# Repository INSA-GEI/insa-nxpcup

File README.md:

# insa-nxpcup

Repository for INSA NXP cup 

# File organization
- **buggy_kl25z**: contain code, documentation, and hardware design of the Buggy with FRMD_KL25Z board (2 oldest buggies) 
- **guides**: useful guides for everyone 
- **archive**: all the work before 2023

# How can I navigate this project?
Each buggy has a dedicated directory with all the code and hardware files.

The source code for a specific buggy can be found at `buggy_name/code/buggy`

It contains the source code for each component and also the main source code of the buggy. 

**There is a README.md in the `code` folder that describes how to work with the code. Please refer to that document.**

# Prerequisite
### *MCU Xpresso*

IDE to work with NXP board, not intuitive to use but has auto-configuration tool.

- **Install [link](https://nxp.flexnetoperations.com/control/frse/product?entitlementId=107109928&lineNum=1&authContactId=81844998&authPartyId=54297698)**
- A guide is available [here](./guides/guide_mcuxpresso.md)

**`WARNING for Windows users!!!`** When installing and using MCU Xpresso, a **firewall window** will pop up that asks you to permit the app to access public and private networks. The same will happen the first time you flash/ debug the code.

**Make sure to permit `both` private and public networks**.

Failed to do so then good luck getting the Redlink server working without reinstalling Windows.

### *Git and GitHub*
- Check [here](./guides/guide_git.md) for a quick guide on how to install and use Git.

# Quick HowTo
Small survival kit for everyone : 
## Installing git (the clean way)
[Get here](https://git-scm.com/downloads) and follow the installer's instructions. One should avoid using the GitHub desktop client.

## Downloading the code
```bash
git clone https://github.com/INSA-GEI/insa-nxpcup.git
cd insa-nxpcup
```

## Update before you start working!
```bash
git pull 
```
If it doesn't work, save your changes elsewhere, and retry with
```bash
git stash	#Cancels all your changes in the repo
git pull	#Try pulling again
```

## Uploading your work
Upload as often as possible. Most errors here appear when working un un-updated code.

```bash
git add .
git commit -m "Message to describe commit"
git push #Sends the previous commit on this repo
```

**NB:** A good commit message is brief, and completes the following statement: *This commit will ...*.

# Branches management
**Do not use the master branch!**

You are in branch master, nothing should be done here

Select a valid branch:
```bash
git checkout branch_name
```

Teamwork should use a main branch and integrate inside every stable work. 

**Create new branches derive from the team's main branch for your work in progress.**

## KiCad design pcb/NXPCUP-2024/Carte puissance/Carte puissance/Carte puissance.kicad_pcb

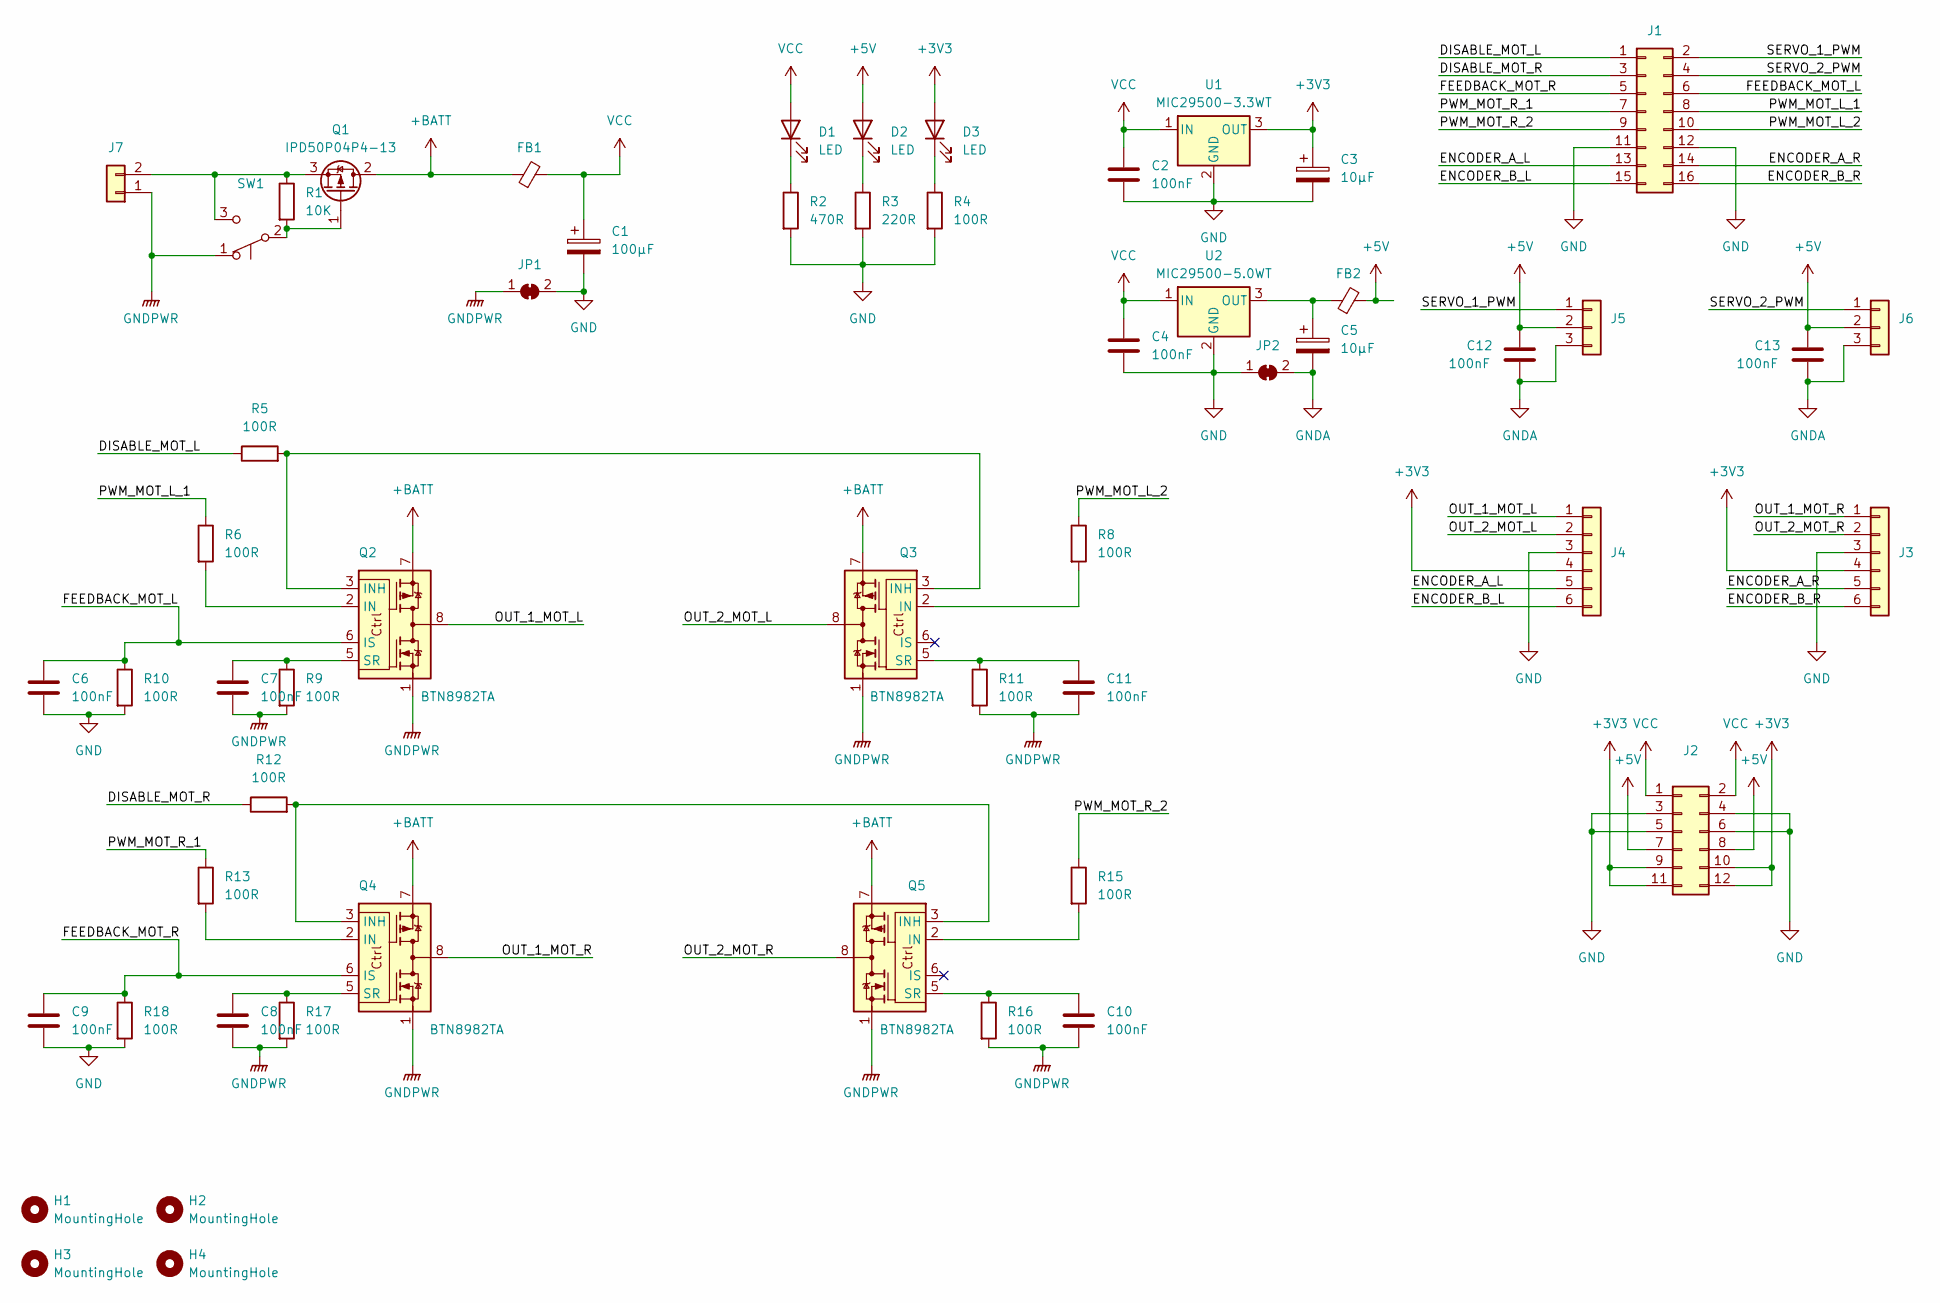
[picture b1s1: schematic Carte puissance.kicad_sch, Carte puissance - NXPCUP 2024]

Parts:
C1: 100µF; CP_Radial_D8.0mm_P3.80mm
C2, C4, C6, C7, C8, C9, C10, C11, C12, C13: 100nF; C_0805_2012Metric
C3, C5: 10µF; CP_Radial_D8.0mm_P3.80mm
D1, D2, D3: LED; LED_D3.0mm
FB1, FB2: FerriteBead_Small; L_1206_3216Metric
H1, H2, H3, H4: MountingHole; MountingHole_3.2mm_M3
J1: Conn_02x08_Odd_Even; PinHeader_2x08_P2.54mm_Vertical
J2: Conn_02x06_Odd_Even; PinHeader_2x06_P2.54mm_Vertical
J3, J4: Conn_01x06; PinHeader_1x06_P2.54mm_Vertical
J5, J6: Conn_01x03; PinHeader_1x03_P2.54mm_Vertical
J7: Conn_01x02; PinHeader_1x02_P2.54mm_Vertical
JP1, JP2: SolderJumper_2_Bridged; SolderJumper-2_P1.3mm_Bridged2Bar_Pad1.0x1.5mm
Q1: IPD50P04P4-13; SOT-23-3
Q2, Q3, Q4, Q5: BTN8982TA; TO-263-7_TabPin8
R1: 10K; R_0805_2012Metric
R2: 470R; R_0805_2012Metric
R3: 220R; R_0805_2012Metric
R4, R5, R6, R8, R9, R10, R11, R12, R13, R15, R16, R17, R18: 100R; R_0805_2012Metric
SW1: SW_Push_SPDT; SW_Slide_1P2T_CK_OS102011MS2Q
U1: MIC29500-3.3WT; TO-252-3_TabPin4
U2: MIC29500-5.0WT; TO-252-3_TabPin4

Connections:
+3V3: C3.1, D3.2 (A), J2.9, J2.10, J2.11, J2.12, J3.4, J4.4, U1.3 (OUT)
+5V: C12.2, C13.2, D2.2 (A), FB2.2, J2.7, J2.8, J5.2, J6.2
+BATT: FB1.1, Q1.2 (D), Q2.7, Q3.7, Q4.7, Q5.7
/DISABLE_MOT_L: J1.1, R5.1
/DISABLE_MOT_R: J1.3, R12.1
/ENCODER_A_L: J1.13, J4.5
/ENCODER_A_R: J1.14, J3.5
/ENCODER_B_L: J1.15, J4.6
/ENCODER_B_R: J1.16, J3.6
/FEEDBACK_MOT_L: C6.1, J1.6, Q2.6 (IS), R10.1
/FEEDBACK_MOT_R: C9.1, J1.5, Q4.6 (IS), R18.1
/OUT_1_MOT_L: J4.1, Q2.4, Q2.8
/OUT_1_MOT_R: J3.1, Q4.4, Q4.8
/OUT_2_MOT_L: J4.2, Q3.4, Q3.8
/OUT_2_MOT_R: J3.2, Q5.4, Q5.8
/PWM_MOT_L_1: J1.8, R6.1
/PWM_MOT_L_2: J1.10, R8.1
/PWM_MOT_R_1: J1.7, R13.1
/PWM_MOT_R_2: J1.9, R15.1
/SERVO_1_PWM: J1.2, J5.1
/SERVO_2_PWM: J1.4, J6.1
GND: C1.2, C2.2, C3.2, C4.2, C6.2, C9.2, J1.11, J1.12, J2.3, J2.4, J2.5, J2.6, J3.3, J4.3, JP1.2 (B), JP2.1 (A), R2.2, R3.2, R4.2, R10.2, R18.2, U1.2 (GND), U2.2 (GND)
GNDA: C5.2, C12.1, C13.1, J5.3, J6.3, JP2.2 (B)
GNDPWR: C7.2, C8.2, C10.2, C11.2, J7.1, JP1.1 (A), Q2.1, Q3.1, Q4.1, Q5.1, R9.2, R11.2, R16.2, R17.2, SW1.1 (A)
unnamed: D1.1 (K), R2.1
unnamed: D2.1 (K), R3.1
unnamed: D3.1 (K), R4.1
unnamed: J7.2, Q1.3 (S), R1.1, SW1.3 (C)
unnamed: Q1.1 (G), R1.2, SW1.2 (B)
unnamed: Q2.2 (IN), R6.2
unnamed: Q2.3 (INH), Q3.3 (INH), R5.2
unnamed: C7.1, Q2.5 (SR), R9.1
unnamed: Q3.2 (IN), R8.2
unnamed: C11.1, Q3.5 (SR), R11.1
unnamed: Q4.2 (IN), R13.2
unnamed: Q4.3 (INH), Q5.3 (INH), R12.2
unnamed: C8.1, Q4.5 (SR), R17.1
unnamed: Q5.2 (IN), R15.2
unnamed: C10.1, Q5.5 (SR), R16.1
unnamed: C5.1, FB2.1, U2.3 (OUT)
VCC: C1.1, C2.1, C4.1, D1.2 (A), FB1.2, J2.1, J2.2, U1.1 (IN), U2.1 (IN)

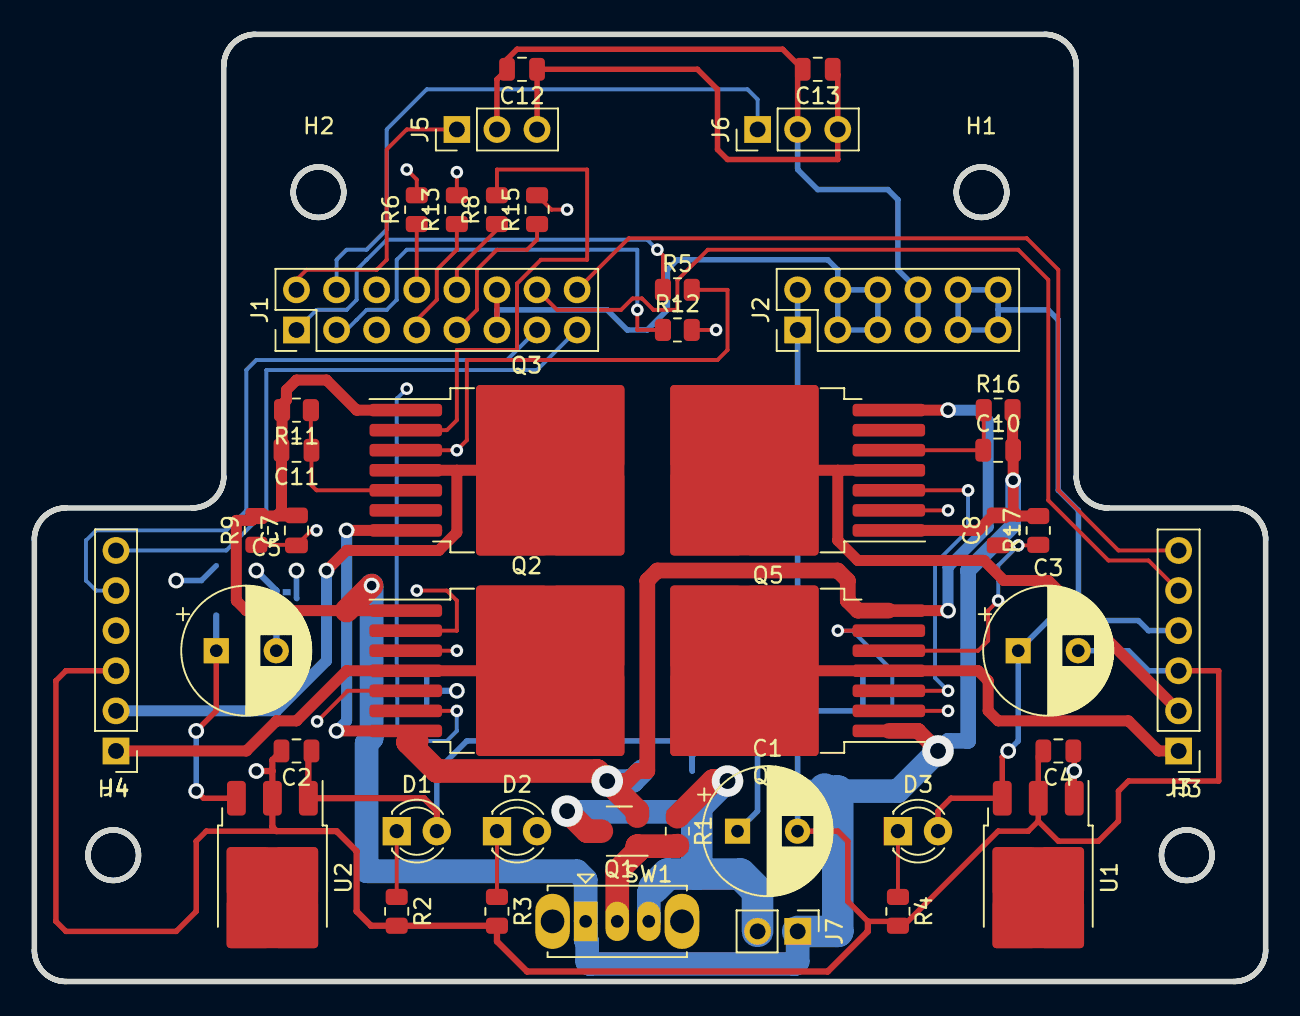
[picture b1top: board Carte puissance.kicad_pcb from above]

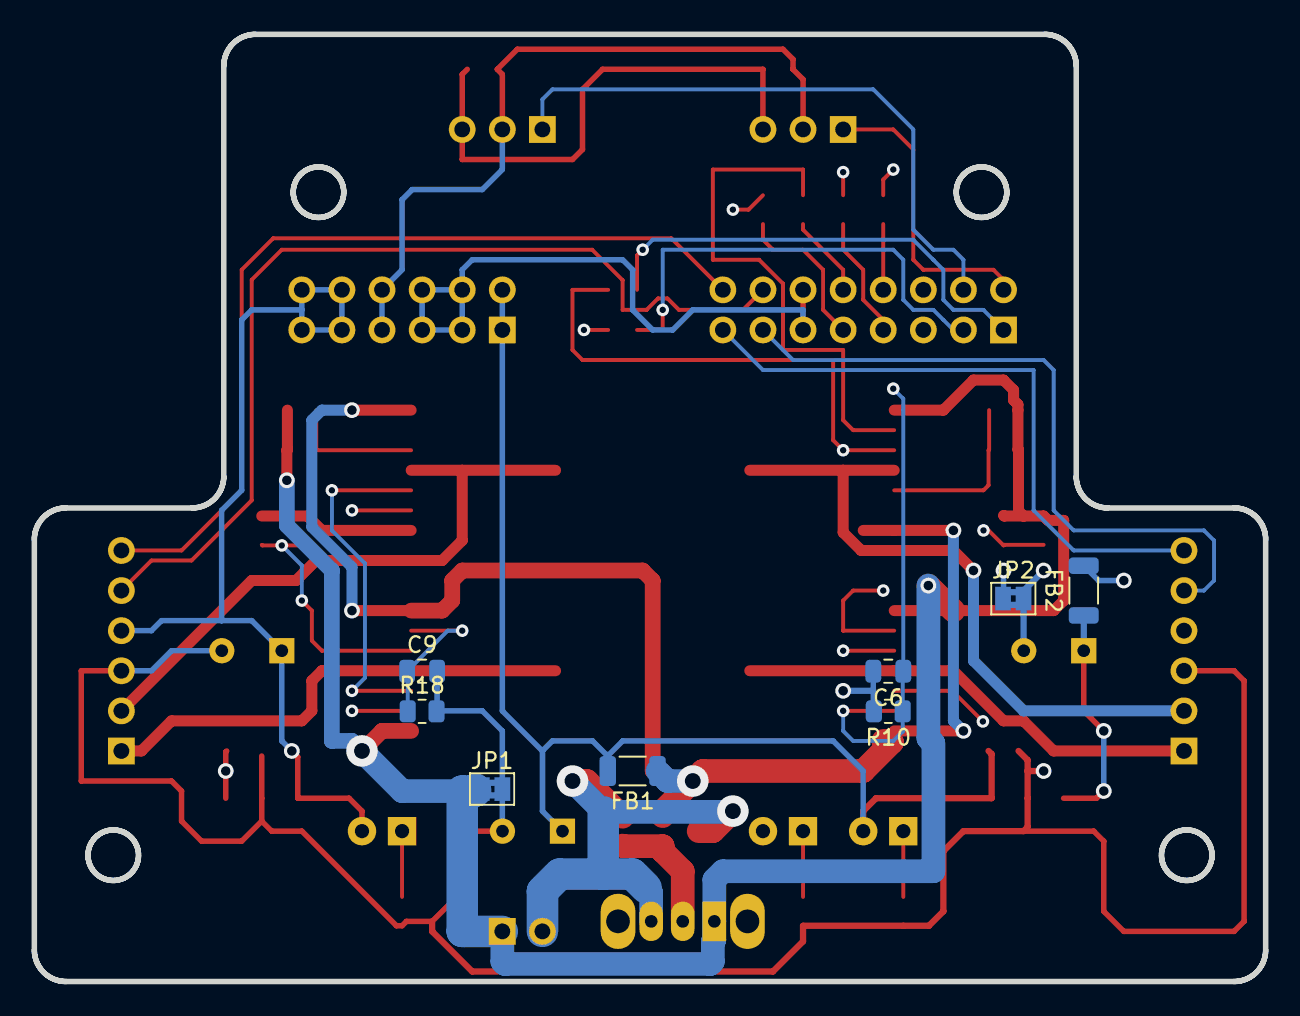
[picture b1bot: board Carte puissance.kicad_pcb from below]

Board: 4 copper layers, 78.0 x 60.0 mm, 55 parts (8 on the bottom side), 41 nets.

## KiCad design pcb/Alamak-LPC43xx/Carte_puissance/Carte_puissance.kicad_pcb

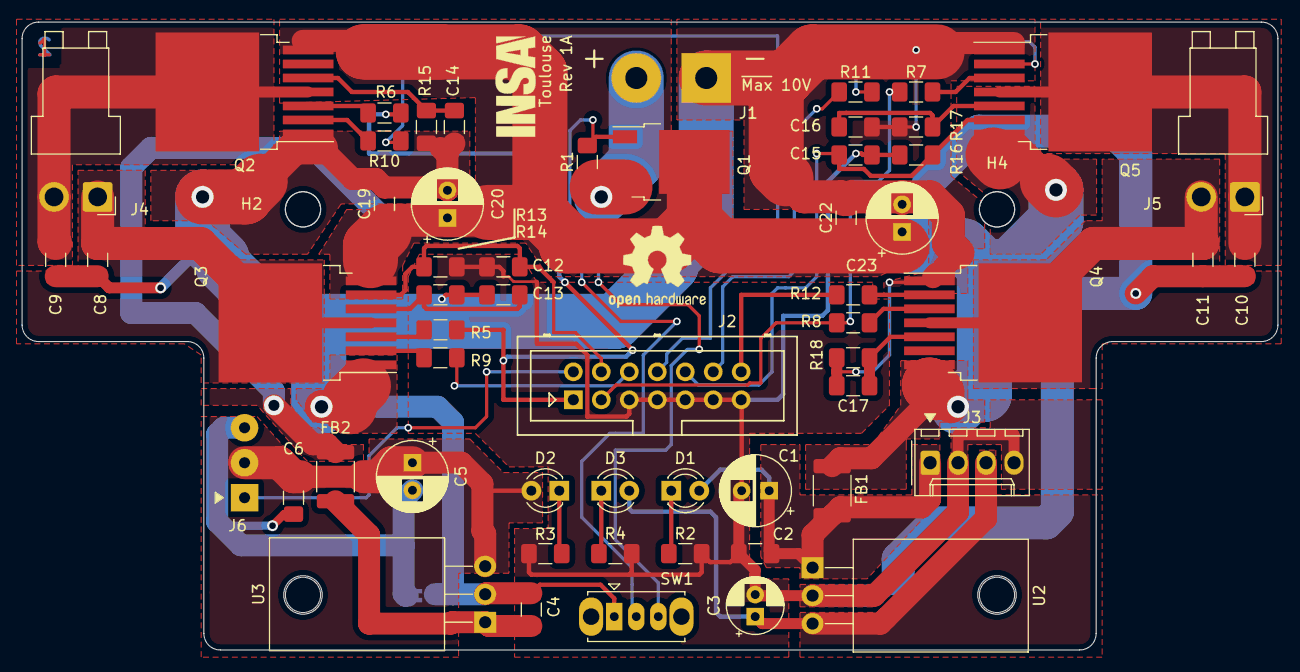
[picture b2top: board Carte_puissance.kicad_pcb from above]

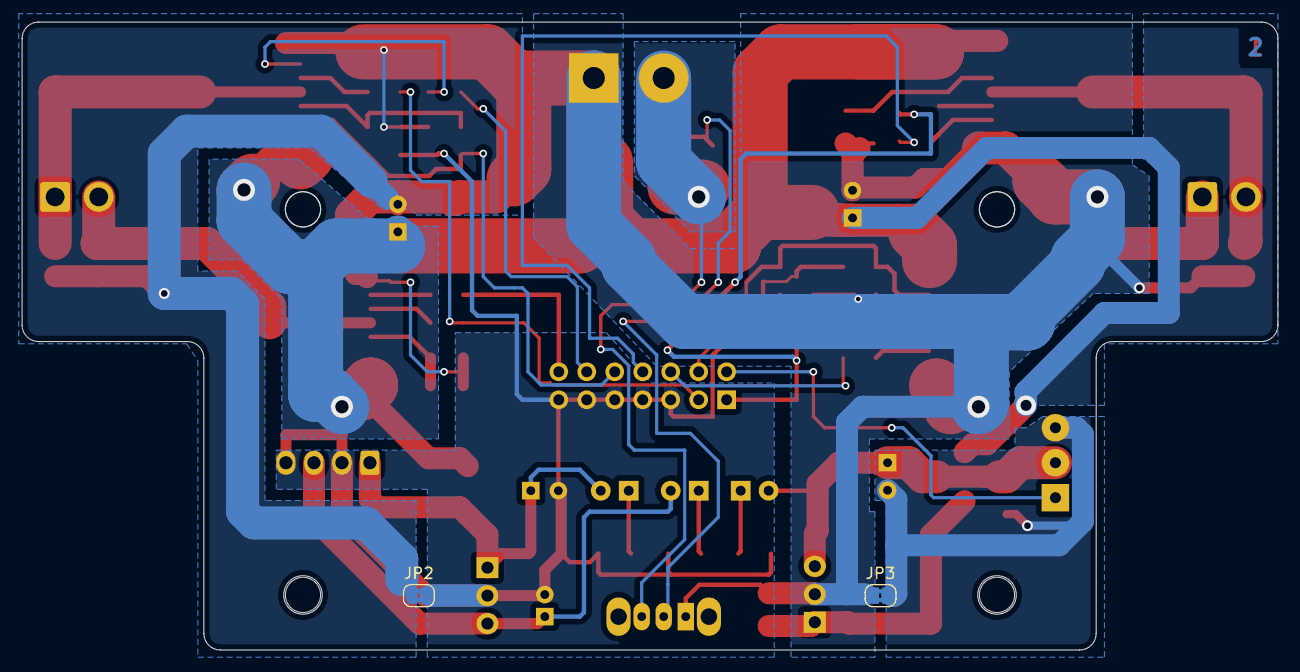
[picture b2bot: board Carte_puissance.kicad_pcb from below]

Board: 2 copper layers, 114.0 x 57.0 mm, 63 parts (2 on the bottom side), 38 nets.

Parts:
C1, C5: 100µF; CP_Radial_D6.3mm_P2.50mm
C2, C4, C6, C8, C9, C10, C11, C13, C14, C16, C17, C19, C22: 100nF; C_1206_3216Metric_Pad1.42x1.75mm_HandSolder
C3: 10µF; CP_Radial_D5.0mm_P2.00mm
C12, C15: 1nF; C_1206_3216Metric_Pad1.42x1.75mm_HandSolder
C20, C23: 470µF; CP_Radial_D6.3mm_P2.50mm
D1, D2, D3: LED; LED_D3.0mm
FB1, FB2: Ferrite_Bead; C_1812_4532Metric_Pad1.30x3.40mm_HandSolder
H2, H4: MountingHole; MountingHole_3.2mm_M3
J1: Conn_01x02; SolderWirePad_1x02_P7.62mm_Drill2mm
J2: Conn_02x07_Odd_Even; Multicomp_MC9A12-1434_2x07_P2.54mm_Vertical
J3: Molex KK 254; Molex_KK-254_AE-6410-04A_1x04_P2.54mm_Vertical
J4: MOT LEFT; JST_VH_B2PS-VH_1x02_P3.96mm_Horizontal
J5: MOT RIGHT; JST_VH_B2PS-VH_1x02_P3.96mm_Horizontal
J6: Conn_01x03; SolderWirePad_1x03_P3.175mm_Drill1mm
JP2, JP3: SolderJumper_2_Bridged; SolderJumper-2_P1.3mm_Bridged2Bar_RoundedPad1.0x1.5mm
Q1: IPD50P04P4-13; TO-252-2
Q2, Q3, Q4, Q5: BTN8982TA; TO-263-7_TabPin8
R1, R5, R6, R7, R8, R9, R10, R11, R12: 10K; R_1206_3216Metric_Pad1.42x1.75mm_HandSolder
R2, R3, R4: 330R; R_1206_3216Metric_Pad1.42x1.75mm_HandSolder
R13, R16: 1K; R_1206_3216Metric_Pad1.42x1.75mm_HandSolder
R14, R15, R17, R18: 510R; R_1206_3216Metric_Pad1.42x1.75mm_HandSolder
REF1: OSHW-Logo2_9.8x8mm_SilkScreen
REF2: LOGO; insa-image
SW1: SW_SPDT; SW_Slide_1P2T_CK_OS102011MS2Q
U2: MIC29500-3.3WT; TO-220-3_Horizontal_TabDown
U3: MIC29500-5.0WT; TO-220-3_Horizontal_TabDown

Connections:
+3V3: C3.1, D3.2, J3.3, U2.3
+5V: C5.1, C6.2, D2.2, J6.2, U3.3
+BATT: C19.1, C20.1, C22.1, C23.1, FB1.2, FB2.2, Q1.2, Q2.7, Q3.7, Q4.7, Q5.7
/DISABLE_MOT_L: J2.1, R5.1, R6.1
/DISABLE_MOT_R: J2.3, R7.1, R8.1
/FEEDBACK_MOT_L: C12.1, J2.4, Q3.6, R13.1
/FEEDBACK_MOT_R: C15.1, J2.10, Q5.6, R16.1
/OUT_1_MOT_L: C8.2, J4.1, Q3.4, Q3.8
/OUT_1_MOT_R: C10.2, J5.1, Q5.4, Q5.8
/OUT_2_MOT_L: C9.1, J4.2, Q2.4, Q2.8
/OUT_2_MOT_R: C11.1, J5.2, Q4.4, Q4.8
/PWM_MOT_L_1: J2.6, R9.1
/PWM_MOT_L_2: J2.8, R10.1
/PWM_MOT_R_1: J2.12, R11.1
/PWM_MOT_R_2: J2.14, R12.1
/SERVO_PWM: J2.2, J6.1
GND: C1.2, C2.2, C3.2, C12.2, C15.2, J2.5, J2.7, J2.9, J2.11, J2.13, J3.2, J3.4, JP2.2, R2.2, R3.2, R4.2, R13.2, R16.2, U2.2
GNDA: C5.2, C6.1, J6.3, JP3.2
GNDPWR: C4.2, C8.1, C9.2, C10.1, C11.2, C13.2, C14.2, C16.2, C17.2, C19.2, C20.2, C22.2, C23.2, J1.1, JP2.1, JP3.1, Q2.1, Q3.1, Q4.1, Q5.1, R14.2, R15.2, R17.2, R18.2, SW1.1, U3.2
unnamed: C4.1, FB2.1, U3.1
unnamed: C13.1, Q3.5, R14.1
unnamed: C14.1, Q2.5, R15.1
unnamed: C16.1, Q5.5, R17.1
unnamed: C17.1, Q4.5, R18.1
unnamed: D1.1, R2.1
unnamed: D2.1, R3.1
unnamed: D3.1, R4.1
unnamed: J1.2, Q1.3, R1.1, SW1.3
unnamed: Q1.1, R1.2, SW1.2
unnamed: Q2.2, R10.2
unnamed: Q2.3, R6.2
unnamed: Q3.2, R9.2
unnamed: Q3.3, R5.2
unnamed: Q4.2, R12.2
unnamed: Q4.3, R8.2
unnamed: Q5.2, R11.2
unnamed: Q5.3, R7.2
VCC: C1.1, C2.1, D1.2, FB1.1, J3.1, U2.1

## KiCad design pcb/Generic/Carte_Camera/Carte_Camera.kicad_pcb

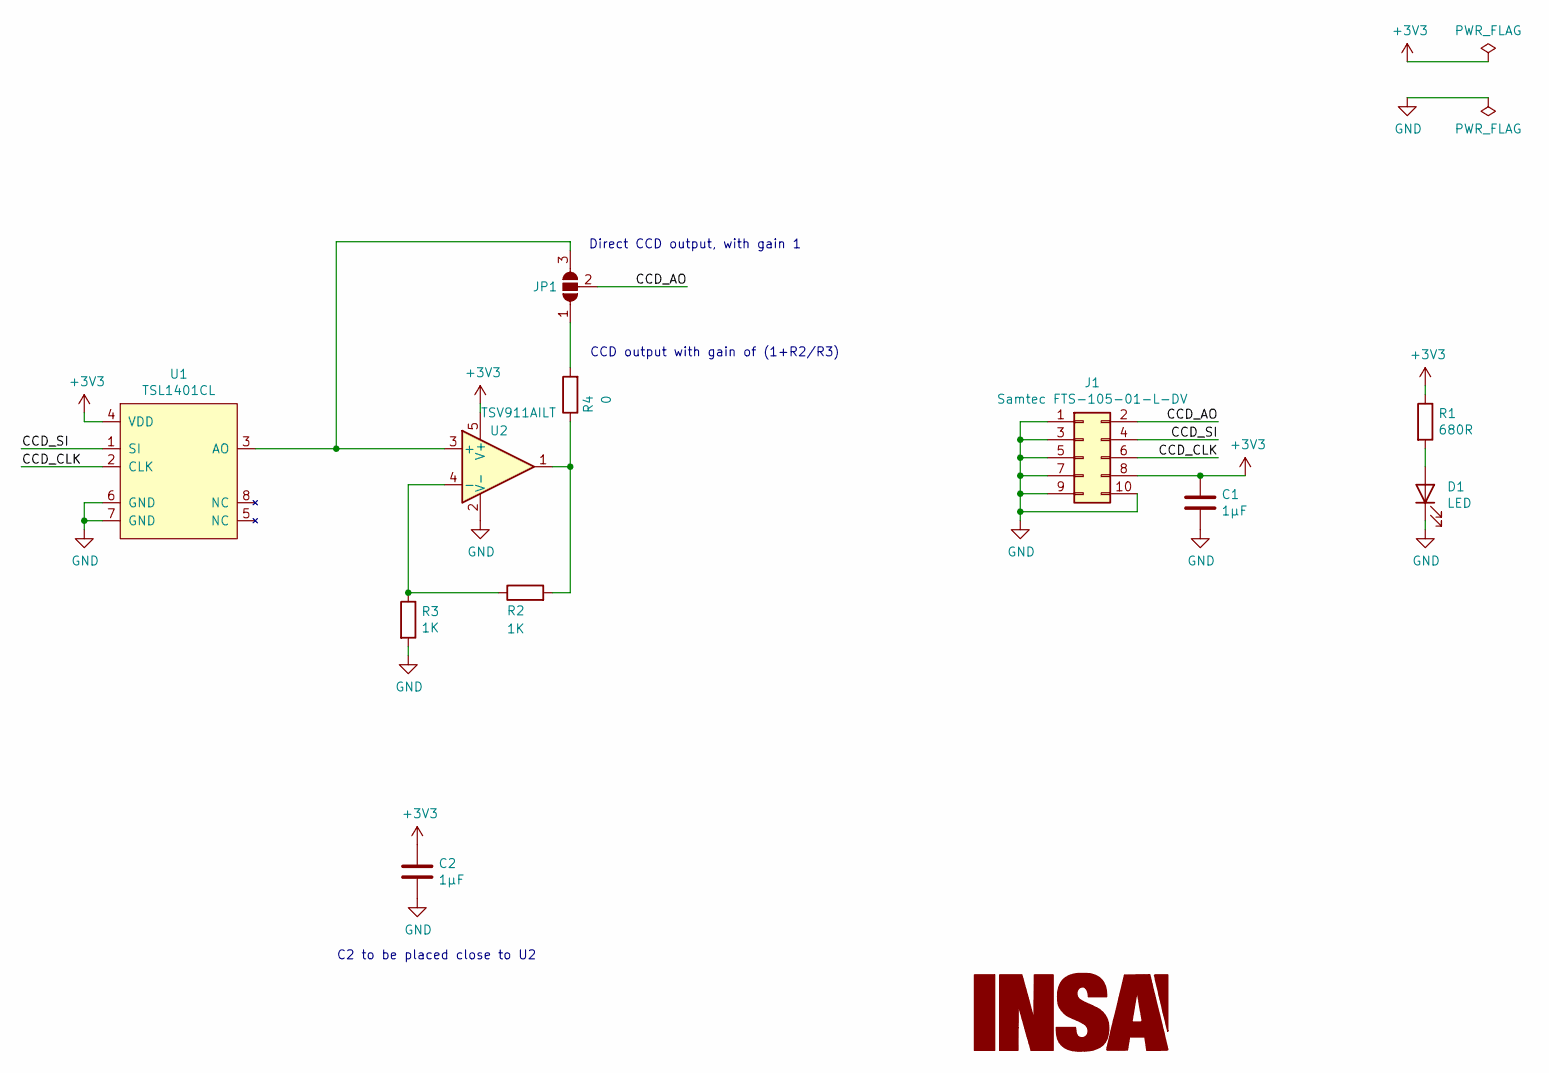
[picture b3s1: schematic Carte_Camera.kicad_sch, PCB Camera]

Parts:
C1, C2: 1µF; C_0805_2012Metric_Pad1.15x1.40mm_HandSolder
D1: LED; LED_0805_2012Metric_Pad1.15x1.40mm_HandSolder
J1: Samtec FTS-105-01-L-DV; PinHeader_2x05_P1.27mm_Vertical
JP1: SolderJumper_3_Open; SolderJumper-3_P1.3mm_Open_RoundedPad1.0x1.5mm_NumberLabels
R1: 680R; R_0805_2012Metric_Pad1.15x1.40mm_HandSolder
R2, R3: 1K; R_0805_2012Metric_Pad1.15x1.40mm_HandSolder
R4: 0; R_0805_2012Metric_Pad1.15x1.40mm_HandSolder
U1: TSL1401CL
U2: TSV911AILT; SOT-23-5

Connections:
+3V3: C1.1, C2.1, J1.8, R1.1, U1.4 (VDD), U2.5 (V+)
/CCD_AO: J1.2, JP1.2 (C)
/CCD_CLK: J1.6, U1.2 (CLK)
/CCD_SI: J1.4, U1.1 (SI)
GND: C1.2, C2.2, D1.1 (K), J1.1, J1.3, J1.5, J1.7, J1.9, J1.10, R3.2, U1.6 (GND), U1.7 (GND), U2.2 (V-)
unnamed: D1.2 (A), R1.2
unnamed: JP1.1 (A), R4.2
unnamed: JP1.3 (B), U1.3 (AO), U2.3 (+)
unnamed: R2.1, R3.1, U2.4 (-)
unnamed: R2.2, R4.1, U2.1

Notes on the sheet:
Direct CCD output, with gain 1
C2 to be placed close to U2
CCD output with gain of (1+R2/R3)

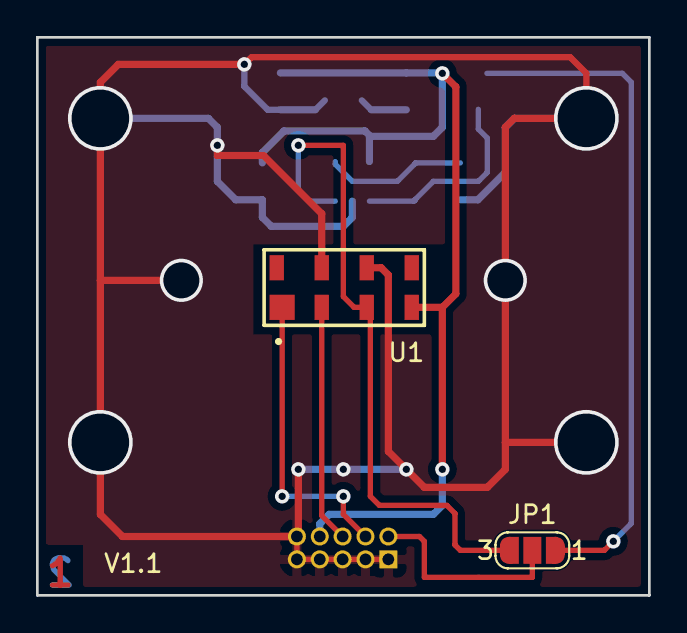
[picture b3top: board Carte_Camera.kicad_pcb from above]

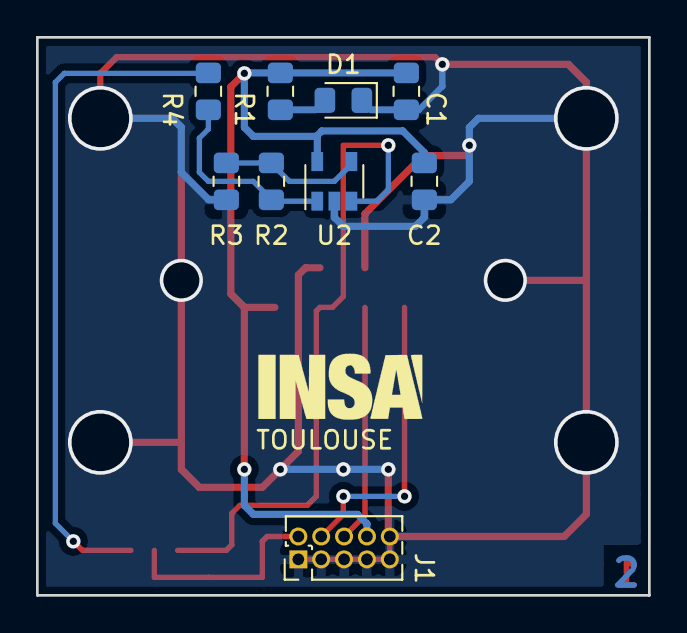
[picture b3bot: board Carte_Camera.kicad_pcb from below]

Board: 2 copper layers, 34.0 x 31.0 mm, 12 parts (10 on the bottom side), 10 nets.

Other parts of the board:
G1: LOGO; insa-image

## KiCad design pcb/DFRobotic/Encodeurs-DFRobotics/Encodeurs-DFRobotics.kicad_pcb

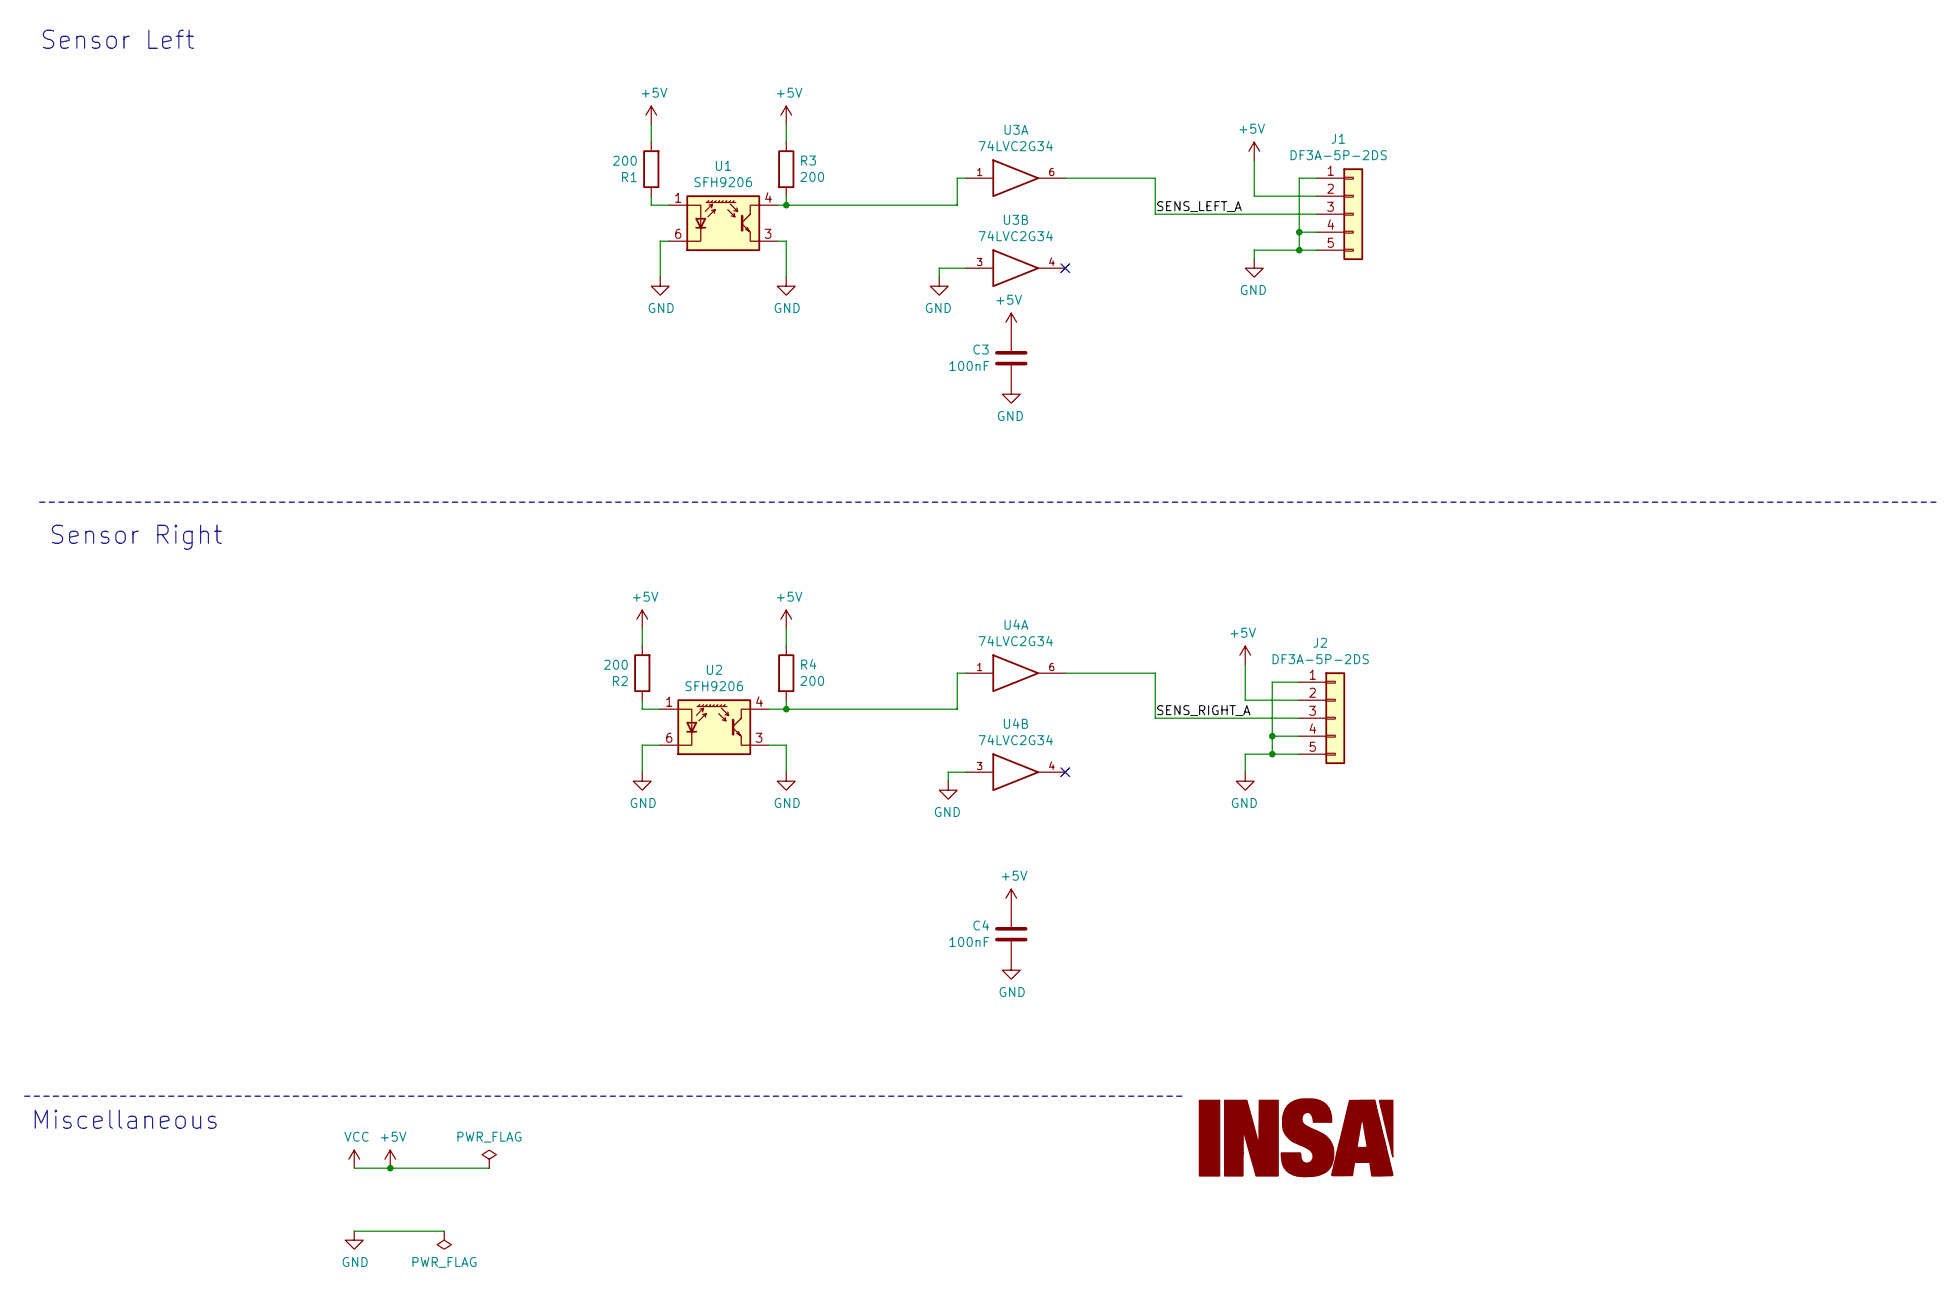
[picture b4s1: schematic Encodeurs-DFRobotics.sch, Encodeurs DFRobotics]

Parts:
C3, C4: 100nF; C_0805_2012Metric_Pad1.15x1.40mm_HandSolder
G1: LOGO
J1, J2: DF3A-5P-2DS
R1, R2, R3, R4: 200; R_0805_2012Metric_Pad1.15x1.40mm_HandSolder
U1, U2: SFH9206; Osram_SFH9x0x
U3, U4: 74LVC2G34; SOT-363_SC-70-6_Handsoldering

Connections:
+5V: C3.1, C4.1, J1.2, J2.2, R1.2, R2.2, R3.1, R4.1, U3.5 (VCC), U4.5 (VCC)
/SENS_LEFT_A: J1.3, U3.6
/SENS_RIGHT_A: J2.3, U4.6
GND: C3.2, C4.2, J1.1, J1.4, J1.5, J2.1, J2.4, J2.5, U1.3 (E), U1.6 (K), U2.3 (E), U2.6 (K), U3.2 (GND), U3.3, U4.2 (GND), U4.3
unnamed: R1.1, U1.1 (A)
unnamed: R2.1, U2.1 (A)
unnamed: R3.2, U1.4 (C), U3.1
unnamed: R4.2, U2.4 (C), U4.1

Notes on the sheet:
Sensor Left
Sensor Right
Miscellaneous

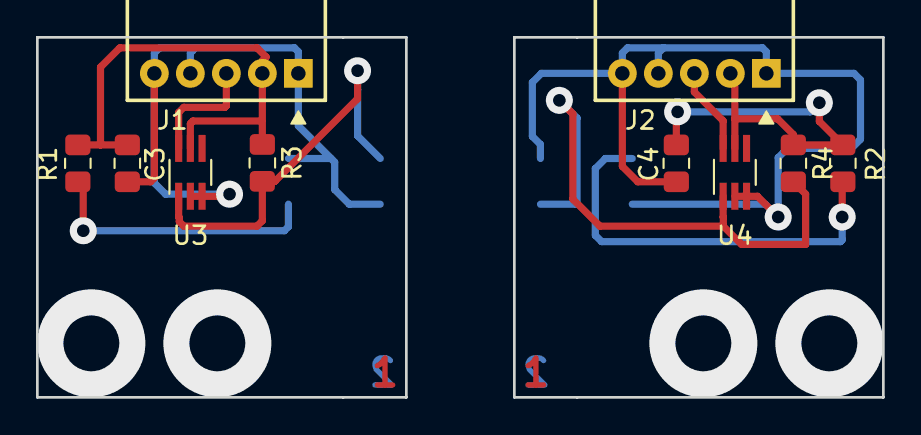
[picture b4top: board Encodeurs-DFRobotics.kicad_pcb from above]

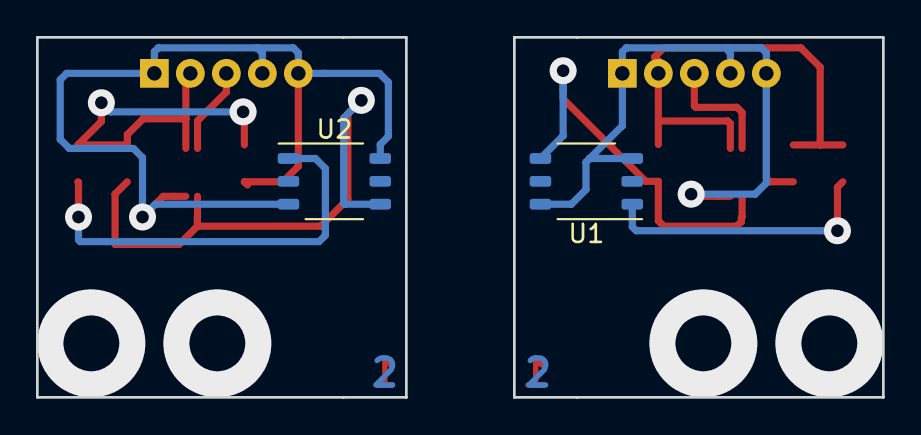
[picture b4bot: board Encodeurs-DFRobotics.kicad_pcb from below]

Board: 2 copper layers, 47.0 x 20.0 mm, 12 parts (2 on the bottom side), 8 nets.
